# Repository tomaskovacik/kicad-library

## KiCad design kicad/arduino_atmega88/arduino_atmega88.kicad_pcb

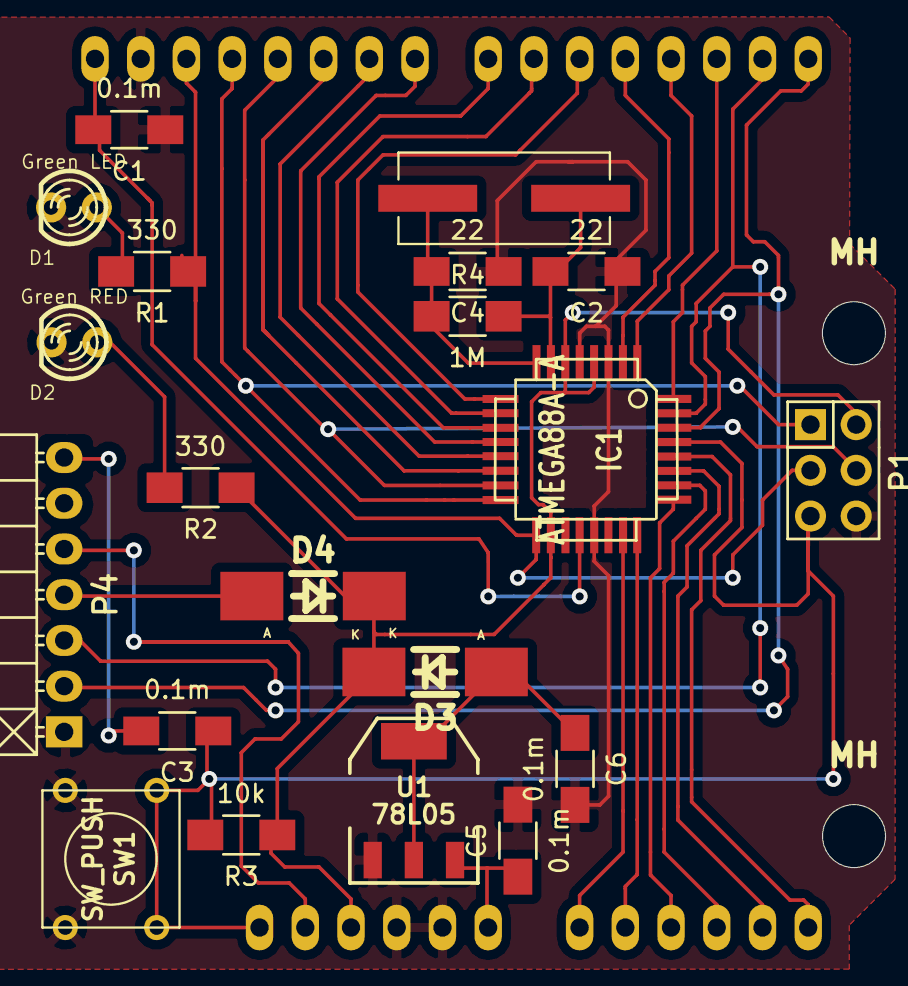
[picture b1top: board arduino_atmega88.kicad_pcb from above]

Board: 2 copper layers, 25 parts (0 on the bottom side), 33 nets.

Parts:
C1, C3, C5, C6: 0.1m; C_1206_HandSoldering
C2, C4: 22; C_1206_HandSoldering
D1: Green LED; LED-3MM
D2: Green RED; LED-3MM
D3, D4: 1N4148; Diode-MELF_Handsoldering
IC1: ATMEGA88A-A; TQFP-32
MH: MountingHole_3-5mm_RevA_Date21Jun2010; MountingHole_3-5mm
MH#2, MH#3, MH#4: MountingHole_3-5mm_RevA_Date21Jun2010; MountingHole_3-5mm
P1: CONN_6; Pin_Header_Straight_2x03
P4: CONN_7; Pin_Header_Angled_1x07
R1, R2: 330; R_1206_HandSoldering
R3: 10k; R_1206_HandSoldering
R4: 1M; R_1206_HandSoldering
SHIELD1: ARDUINO_SHIELD; ARDUINO_SHIELD_2_040pins
SW1: SW_PUSH; SW_PUSH_SMALL
U1: 78L05; SOT-223-REGULATOR
X1: 16MHz; xtal2-11.5mmx4.83mm

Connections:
+3.3V: P4.5, SHIELD1.3V3
+5V: D3.2, D4.2, IC1.4, IC1.6, IC1.18, P1.2, R2.1, R3.1, SHIELD1.5V
/A0: IC1.23, SHIELD1.AD0
/A1: IC1.24, SHIELD1.AD1
/A2: IC1.25, SHIELD1.AD2
/A3: IC1.26, SHIELD1.AD3
/A4: IC1.27, SHIELD1.AD4
/A5: IC1.28, SHIELD1.AD5
/AREF: C1.2, IC1.20, SHIELD1.AREF
/D2: IC1.32, SHIELD1.2
/D3: IC1.1, SHIELD1.3
/D4: IC1.2, SHIELD1.4
/D5: IC1.9, SHIELD1.5
/D6: IC1.10, SHIELD1.6
/D7: IC1.11, SHIELD1.7
/D8: IC1.12, SHIELD1.8
/D9: IC1.13, SHIELD1.9
/D10: IC1.14, SHIELD1.10
/DTR: C3.2, P4.7
/MISO: IC1.16, P1.1, SHIELD1.12
/MOSI: IC1.15, P1.4, SHIELD1.11
/RESET: C3.1, IC1.29, P1.5, R3.2, SHIELD1.RST, SW1.1
/RX: IC1.30, P4.2, SHIELD1.0
/SCK: IC1.17, P1.3, R1.1, SHIELD1.13
/TX: IC1.31, P4.3, SHIELD1.1
/Vin: C5.1, SHIELD1.V_IN, U1.VI
GND: C1.1, C2.1, C4.1, C5.2, C6.2, D1.2, D2.2, IC1.3, IC1.5, IC1.21, P1.6, P4.1, SHIELD1.GND1, SHIELD1.GND2, SHIELD1.GND3, SW1.2, U1.GND
unnamed: C2.2, IC1.7, R4.2, X1.1
unnamed: C4.2, IC1.8, R4.1, X1.2
unnamed: C6.1, D3.1, U1.VO
unnamed: D1.1, R1.2
unnamed: D2.1, R2.2
unnamed: D4.1, P4.4

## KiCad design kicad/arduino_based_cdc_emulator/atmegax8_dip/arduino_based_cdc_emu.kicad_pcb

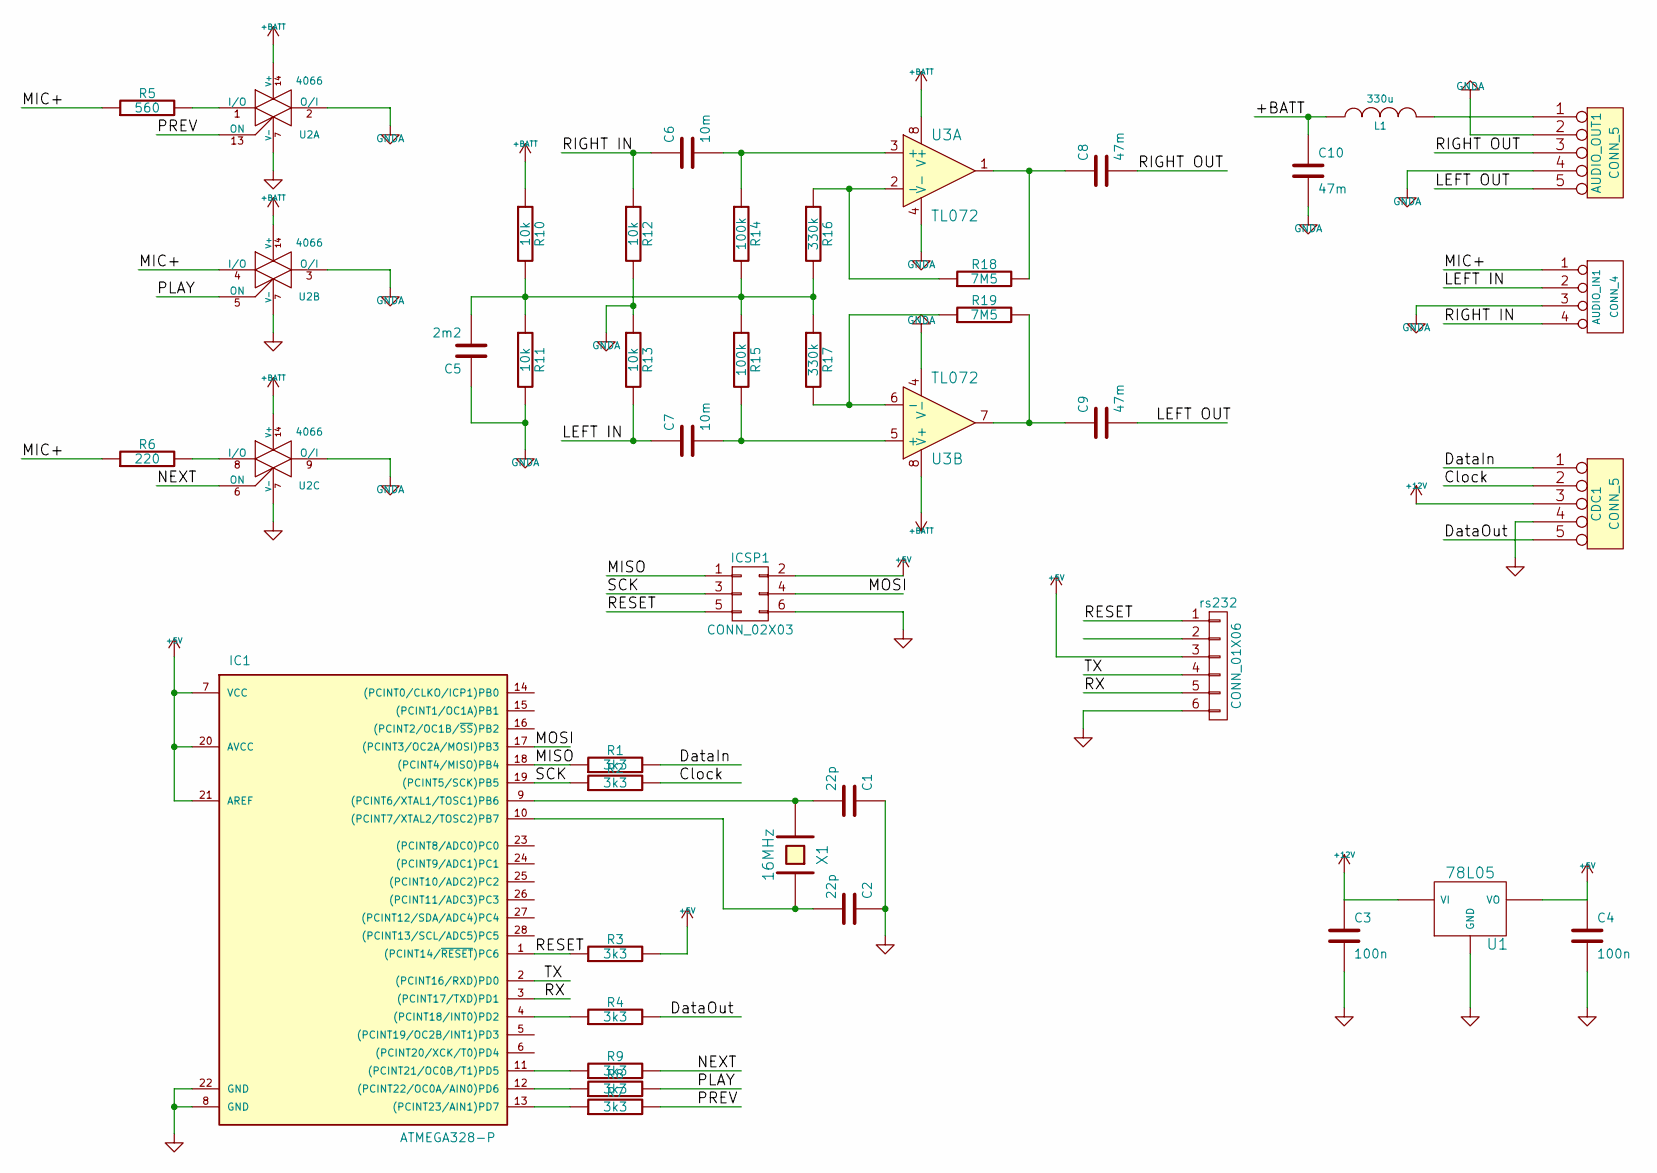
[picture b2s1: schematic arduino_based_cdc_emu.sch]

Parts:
AUDIO_IN1: CONN_4; Pin_Header_Straight_1x04
AUDIO_OUT1: CONN_5; Pin_Header_Straight_1x05
C1, C2: 22p; C1
C3, C4: 100n; C1
C5: 2m2; C1V5
C6, C7: 10m; C1V8
C8, C9, C10: 47m; C2V8
CDC1: CONN_5; Pin_Header_Straight_1x05
IC1: ATMEGA328-P; DIP-28__300
ICSP1: CONN_02X03; Pin_Header_Straight_2x03
L1: 330u; R3-5
R1, R2, R3, R4, R7, R8, R9: 3k3; R3
R5: 560; R3
R6: 220; R3
R10, R11, R12: 10k; R3
R13: 10k; Resistor_Vertical_RM5mm
R14, R15: 100k; R3
R16, R17: 330k; R3
R18, R19: 7M5; R3
U1: 78L05; TO92-STABIL
U2: 4066; DIP-14__300
U3: TL072; DIP-8__300
X1: 16MHz; HC-49V
rs232: CONN_01X06; Pin_Header_Straight_1x06

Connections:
+5V: C4.1, IC1.7 (VCC), IC1.20 (AVCC), IC1.21 (AREF), ICSP1.2, R3.2, U1.VO, rs232.3
+12V: C3.1, CDC1.3, U1.VI
+BATT: C10.1, L1.1, R10.1, U2.14 (V+), U3.8 (V+)
/Clock: CDC1.2, R2.2
/DataIn: CDC1.1, R1.2
/DataOut: CDC1.5, R4.2
/LEFT IN: AUDIO_IN1.2, C7.1, R13.2
/LEFT OUT: AUDIO_OUT1.5, C9.2
/MIC+: AUDIO_IN1.1, R5.1, R6.1, U2.4 (I/O)
/MISO: IC1.18 ((PCINT4/MISO)PB4), ICSP1.1, R1.1
/MOSI: IC1.17 ((PCINT3/OC2A/MOSI)PB3), ICSP1.4
/NEXT: R9.2, U2.6 (ON)
/PLAY: R8.2, U2.5 (ON)
/PREV: R7.2, U2.13 (ON)
/RESET: IC1.1 ((PCINT14/~RESET~)PC6), ICSP1.5, R3.1, rs232.1
/RIGHT IN: AUDIO_IN1.4, C6.1, R12.1
/RIGHT OUT: AUDIO_OUT1.3, C8.2
/RX: IC1.3 ((PCINT17/TXD)PD1), rs232.5
/SCK: IC1.19 ((PCINT5/SCK)PB5), ICSP1.3, R2.1
/TX: IC1.2 ((PCINT16/RXD)PD0), rs232.4
GND: C1.1, C2.1, C3.2, C4.2, CDC1.4, IC1.8 (GND), IC1.22 (GND), ICSP1.6, U1.GND, U2.7 (V-), rs232.6
GNDA: AUDIO_IN1.3, AUDIO_OUT1.2, AUDIO_OUT1.4, C5.1, C10.2, R11.2, R12.2, R13.1, U2.2 (O/I), U2.3 (O/I), U2.9 (O/I), U3.4 (V-)
unnamed: AUDIO_OUT1.1, L1.2
unnamed: C1.2, IC1.9 ((PCINT6/XTAL1/TOSC1)PB6), X1.2
unnamed: C2.2, IC1.10 ((PCINT7/XTAL2/TOSC2)PB7), X1.1
unnamed: C5.2, R10.2, R11.1, R14.2, R15.1, R16.2, R17.1
unnamed: C6.2, R14.1, U3.3 (+)
unnamed: C7.2, R15.2, U3.5 (+)
unnamed: C8.1, R18.2, U3.1
unnamed: C9.1, R19.2, U3.7
unnamed: IC1.4 ((PCINT18/INT0)PD2), R4.1
unnamed: IC1.11 ((PCINT21/OC0B/T1)PD5), R9.1
unnamed: IC1.12 ((PCINT22/OC0A/AIN0)PD6), R8.1
unnamed: IC1.13 ((PCINT23/AIN1)PD7), R7.1
unnamed: R5.2, U2.1 (I/O)
unnamed: R6.2, U2.8 (I/O)
unnamed: R16.1, R18.1, U3.2 (-)
unnamed: R17.2, R19.1, U3.6 (-)

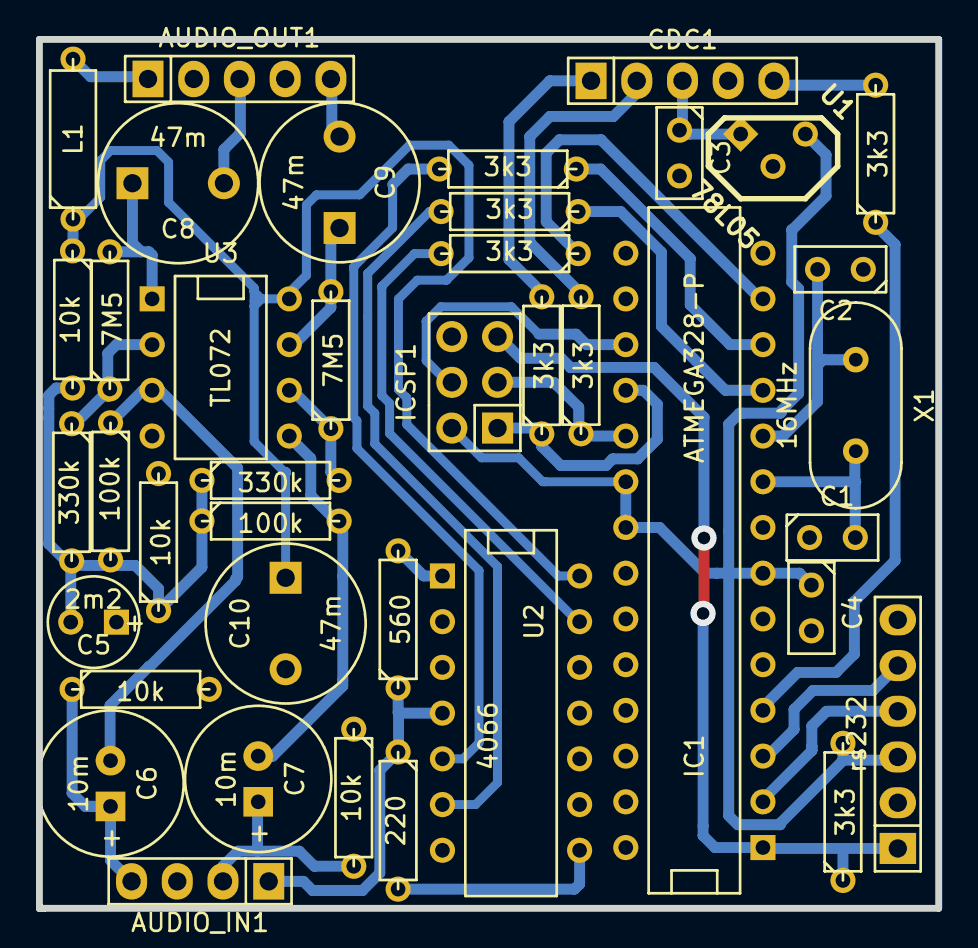
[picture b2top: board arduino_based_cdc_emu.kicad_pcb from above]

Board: 2 copper layers, 50.0 x 48.3 mm, 40 parts (0 on the bottom side), 38 nets.

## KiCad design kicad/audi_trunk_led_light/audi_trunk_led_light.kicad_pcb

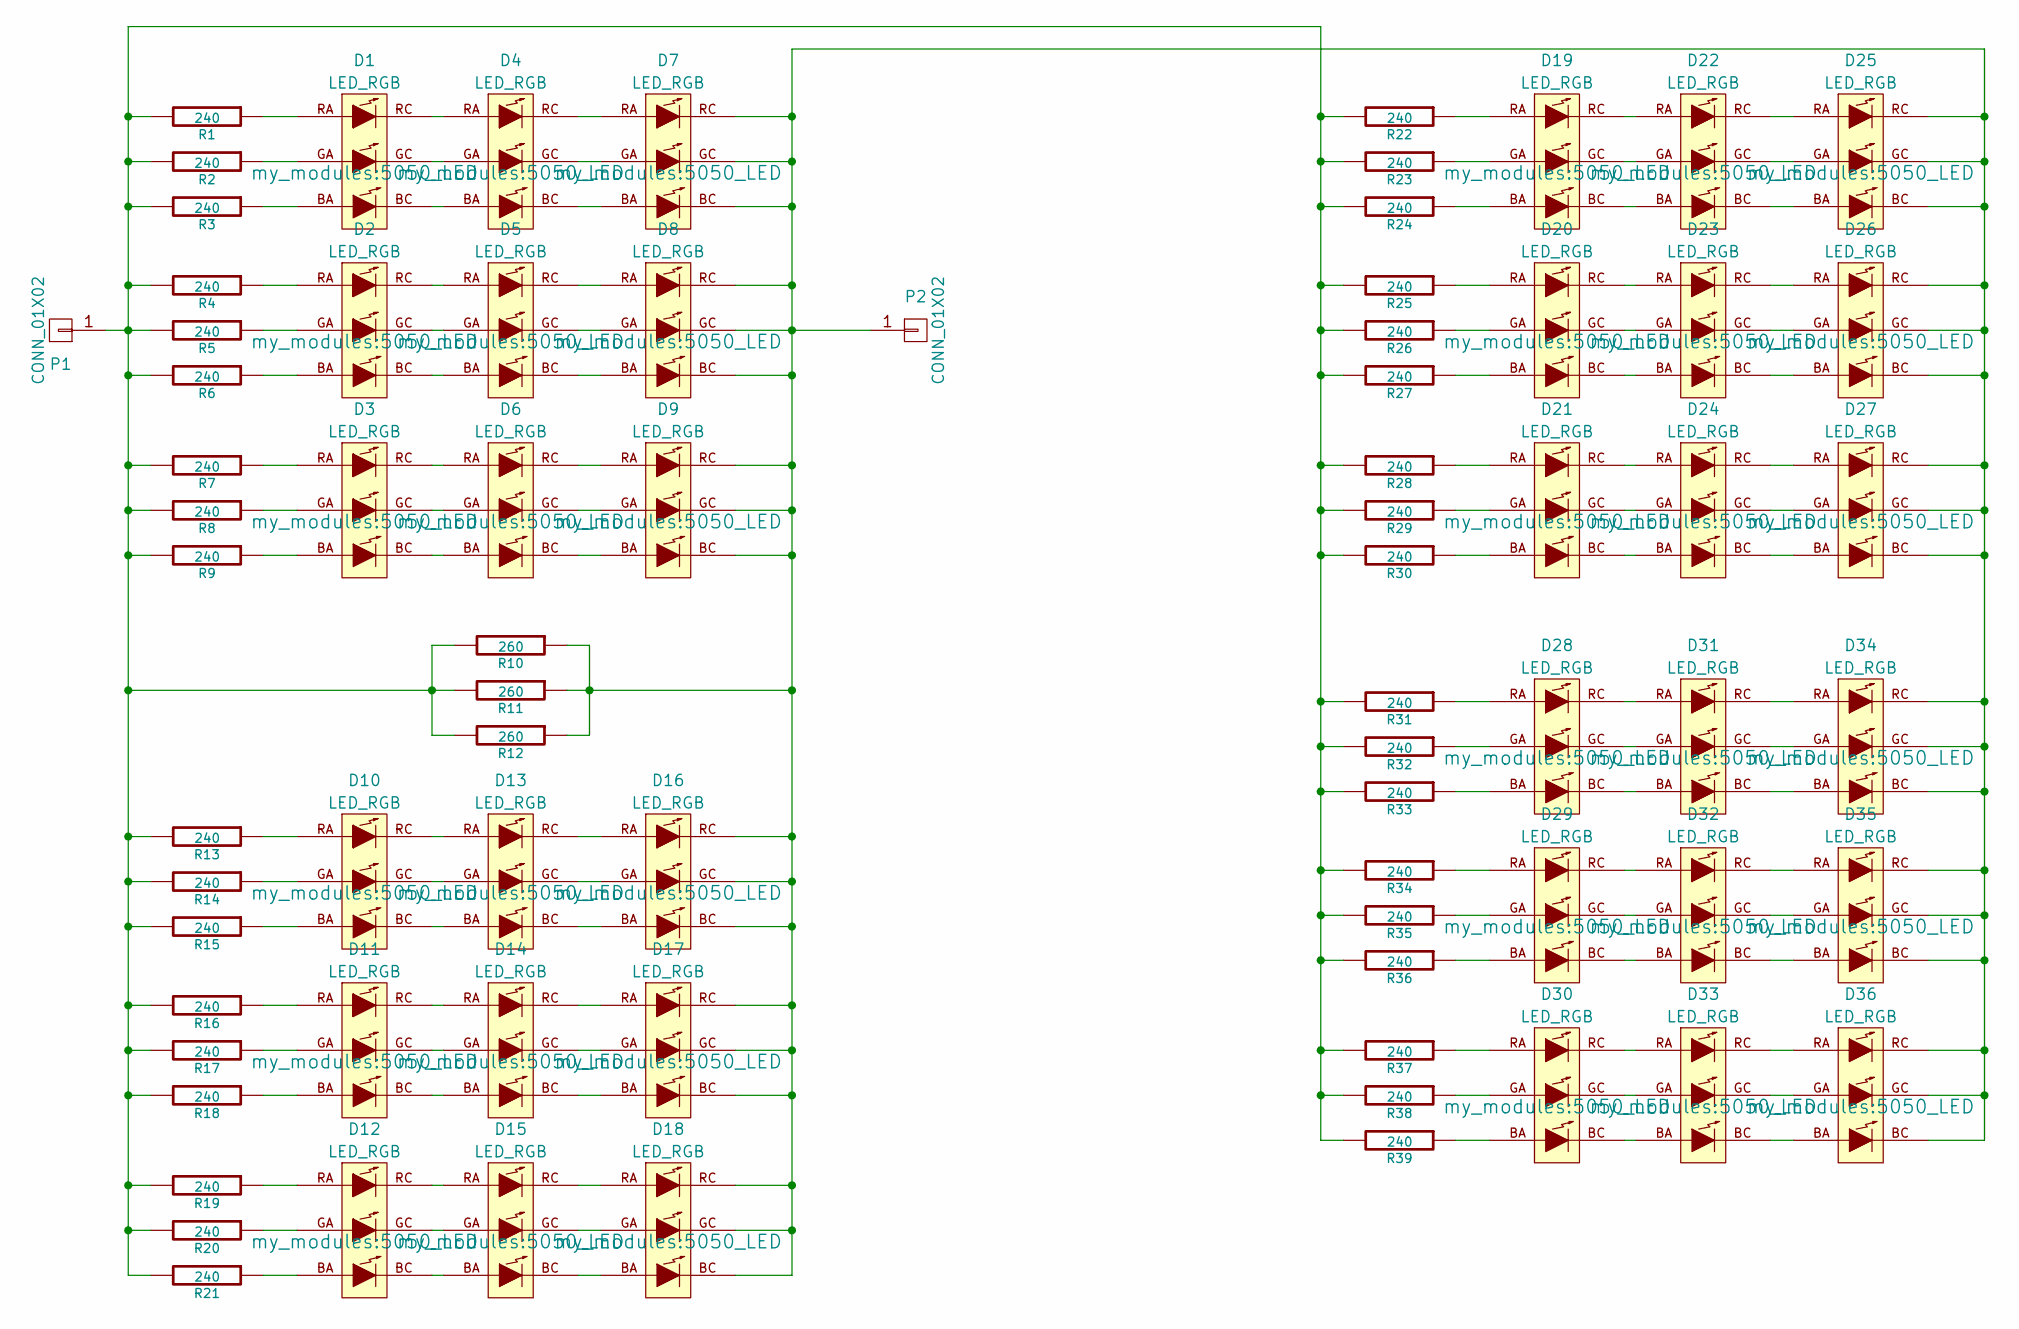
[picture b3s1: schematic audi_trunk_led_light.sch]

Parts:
D1, D2, D3, D4, D5, D6, D7, D8, D9, D10, D11, D12, D13, D14, D15, D16, D17, D18, D19, D20, D21, D22, D23, D24, D25, D26, D27, D28, D29, D30, D31, D32, D33, D34, D35, D36: LED_RGB; 5050_LED
P1, P2: CONN_01X02
R1, R2, R3, R4, R5, R6, R7, R8, R9, R13, R14, R15, R16, R17, R18, R19, R20, R21, R22, R23, R24, R25, R26, R27, R28, R29, R30, R31, R32, R33, R34, R35, R36, R37, R38, R39: 240
R10, R11, R12: 260

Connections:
unnamed: D1.BA (BLUE_ANODE), R3.1
unnamed: D1.BC (BLUE_CATHODE), D4.BA (BLUE_ANODE)
unnamed: D1.GA (GREEN_ANODE), R2.1
unnamed: D1.GC (GREEN_CATHODE), D4.GA (GREEN_ANODE)
unnamed: D1.RA (RED_ANODE), R1.1
unnamed: D1.RC (RED_CATHODE), D4.RA (RED_ANODE)
unnamed: D2.BA (BLUE_ANODE), R6.1
unnamed: D2.BC (BLUE_CATHODE), D5.BA (BLUE_ANODE)
unnamed: D2.GA (GREEN_ANODE), R5.1
unnamed: D2.GC (GREEN_CATHODE), D5.GA (GREEN_ANODE)
unnamed: D2.RA (RED_ANODE), R4.1
unnamed: D2.RC (RED_CATHODE), D5.RA (RED_ANODE)
unnamed: D3.BA (BLUE_ANODE), R9.1
unnamed: D3.BC (BLUE_CATHODE), D6.BA (BLUE_ANODE)
unnamed: D3.GA (GREEN_ANODE), R8.1
unnamed: D3.GC (GREEN_CATHODE), D6.GA (GREEN_ANODE)
unnamed: D3.RA (RED_ANODE), R7.1
unnamed: D3.RC (RED_CATHODE), D6.RA (RED_ANODE)
unnamed: D4.BC (BLUE_CATHODE), D7.BA (BLUE_ANODE)
unnamed: D4.GC (GREEN_CATHODE), D7.GA (GREEN_ANODE)
unnamed: D4.RC (RED_CATHODE), D7.RA (RED_ANODE)
unnamed: D5.BC (BLUE_CATHODE), D8.BA (BLUE_ANODE)
unnamed: D5.GC (GREEN_CATHODE), D8.GA (GREEN_ANODE)
unnamed: D5.RC (RED_CATHODE), D8.RA (RED_ANODE)
unnamed: D6.BC (BLUE_CATHODE), D9.BA (BLUE_ANODE)
unnamed: D6.GC (GREEN_CATHODE), D9.GA (GREEN_ANODE)
unnamed: D6.RC (RED_CATHODE), D9.RA (RED_ANODE)
unnamed: D10.BA (BLUE_ANODE), R15.1
unnamed: D10.BC (BLUE_CATHODE), D13.BA (BLUE_ANODE)
unnamed: D10.GA (GREEN_ANODE), R14.1
unnamed: D10.GC (GREEN_CATHODE), D13.GA (GREEN_ANODE)
unnamed: D10.RA (RED_ANODE), R13.1
unnamed: D10.RC (RED_CATHODE), D13.RA (RED_ANODE)
unnamed: D11.BA (BLUE_ANODE), R18.1
unnamed: D11.BC (BLUE_CATHODE), D14.BA (BLUE_ANODE)
unnamed: D11.GA (GREEN_ANODE), R17.1
unnamed: D11.GC (GREEN_CATHODE), D14.GA (GREEN_ANODE)
unnamed: D11.RA (RED_ANODE), R16.1
unnamed: D11.RC (RED_CATHODE), D14.RA (RED_ANODE)
unnamed: D12.BA (BLUE_ANODE), R21.1
unnamed: D12.BC (BLUE_CATHODE), D15.BA (BLUE_ANODE)
unnamed: D12.GA (GREEN_ANODE), R20.1
unnamed: D12.GC (GREEN_CATHODE), D15.GA (GREEN_ANODE)
unnamed: D12.RA (RED_ANODE), R19.1
unnamed: D12.RC (RED_CATHODE), D15.RA (RED_ANODE)
unnamed: D13.BC (BLUE_CATHODE), D16.BA (BLUE_ANODE)
unnamed: D13.GC (GREEN_CATHODE), D16.GA (GREEN_ANODE)
unnamed: D13.RC (RED_CATHODE), D16.RA (RED_ANODE)
unnamed: D14.BC (BLUE_CATHODE), D17.BA (BLUE_ANODE)
unnamed: D14.GC (GREEN_CATHODE), D17.GA (GREEN_ANODE)
unnamed: D14.RC (RED_CATHODE), D17.RA (RED_ANODE)
unnamed: D15.BC (BLUE_CATHODE), D18.BA (BLUE_ANODE)
unnamed: D15.GC (GREEN_CATHODE), D18.GA (GREEN_ANODE)
unnamed: D15.RC (RED_CATHODE), D18.RA (RED_ANODE)
unnamed: D7.BC (BLUE_CATHODE), D7.GC (GREEN_CATHODE), D7.RC (RED_CATHODE), D8.BC (BLUE_CATHODE), D8.GC (GREEN_CATHODE), D8.RC (RED_CATHODE), D9.BC (BLUE_CATHODE), D9.GC (GREEN_CATHODE), D9.RC (RED_CATHODE), D16.BC (BLUE_CATHODE), D16.GC (GREEN_CATHODE), D16.RC (RED_CATHODE), D17.BC (BLUE_CATHODE), D17.GC (GREEN_CATHODE), D17.RC (RED_CATHODE), D18.BC (BLUE_CATHODE), D18.GC (GREEN_CATHODE), D18.RC (RED_CATHODE), D25.BC (BLUE_CATHODE), D25.GC (GREEN_CATHODE), D25.RC (RED_CATHODE), D26.BC (BLUE_CATHODE), D26.GC (GREEN_CATHODE), D26.RC (RED_CATHODE), D27.BC (BLUE_CATHODE), D27.GC (GREEN_CATHODE), D27.RC (RED_CATHODE), D34.BC (BLUE_CATHODE), D34.GC (GREEN_CATHODE), D34.RC (RED_CATHODE), D35.BC (BLUE_CATHODE), D35.GC (GREEN_CATHODE), D35.RC (RED_CATHODE), D36.BC (BLUE_CATHODE), D36.GC (GREEN_CATHODE), D36.RC (RED_CATHODE), P2.1, R10.1, R11.1, R12.1
unnamed: D19.BA (BLUE_ANODE), R24.1
unnamed: D19.BC (BLUE_CATHODE), D22.BA (BLUE_ANODE)
unnamed: D19.GA (GREEN_ANODE), R23.1
unnamed: D19.GC (GREEN_CATHODE), D22.GA (GREEN_ANODE)
unnamed: D19.RA (RED_ANODE), R22.1
unnamed: D19.RC (RED_CATHODE), D22.RA (RED_ANODE)
unnamed: D20.BA (BLUE_ANODE), R27.1
unnamed: D20.BC (BLUE_CATHODE), D23.BA (BLUE_ANODE)
unnamed: D20.GA (GREEN_ANODE), R26.1
unnamed: D20.GC (GREEN_CATHODE), D23.GA (GREEN_ANODE)
unnamed: D20.RA (RED_ANODE), R25.1
unnamed: D20.RC (RED_CATHODE), D23.RA (RED_ANODE)
unnamed: D21.BA (BLUE_ANODE), R30.1
unnamed: D21.BC (BLUE_CATHODE), D24.BA (BLUE_ANODE)
unnamed: D21.GA (GREEN_ANODE), R29.1
unnamed: D21.GC (GREEN_CATHODE), D24.GA (GREEN_ANODE)
unnamed: D21.RA (RED_ANODE), R28.1
unnamed: D21.RC (RED_CATHODE), D24.RA (RED_ANODE)
unnamed: D22.BC (BLUE_CATHODE), D25.BA (BLUE_ANODE)
unnamed: D22.GC (GREEN_CATHODE), D25.GA (GREEN_ANODE)
unnamed: D22.RC (RED_CATHODE), D25.RA (RED_ANODE)
unnamed: D23.BC (BLUE_CATHODE), D26.BA (BLUE_ANODE)
unnamed: D23.GC (GREEN_CATHODE), D26.GA (GREEN_ANODE)
unnamed: D23.RC (RED_CATHODE), D26.RA (RED_ANODE)
unnamed: D24.BC (BLUE_CATHODE), D27.BA (BLUE_ANODE)
unnamed: D24.GC (GREEN_CATHODE), D27.GA (GREEN_ANODE)
unnamed: D24.RC (RED_CATHODE), D27.RA (RED_ANODE)
unnamed: D28.BA (BLUE_ANODE), R33.1
unnamed: D28.BC (BLUE_CATHODE), D31.BA (BLUE_ANODE)
unnamed: D28.GA (GREEN_ANODE), R32.1
unnamed: D28.GC (GREEN_CATHODE), D31.GA (GREEN_ANODE)
unnamed: D28.RA (RED_ANODE), R31.1
unnamed: D28.RC (RED_CATHODE), D31.RA (RED_ANODE)
unnamed: D29.BA (BLUE_ANODE), R36.1
unnamed: D29.BC (BLUE_CATHODE), D32.BA (BLUE_ANODE)
unnamed: D29.GA (GREEN_ANODE), R35.1
unnamed: D29.GC (GREEN_CATHODE), D32.GA (GREEN_ANODE)
unnamed: D29.RA (RED_ANODE), R34.1
unnamed: D29.RC (RED_CATHODE), D32.RA (RED_ANODE)
unnamed: D30.BA (BLUE_ANODE), R39.1
unnamed: D30.BC (BLUE_CATHODE), D33.BA (BLUE_ANODE)
unnamed: D30.GA (GREEN_ANODE), R38.1
unnamed: D30.GC (GREEN_CATHODE), D33.GA (GREEN_ANODE)
unnamed: D30.RA (RED_ANODE), R37.1
unnamed: D30.RC (RED_CATHODE), D33.RA (RED_ANODE)
unnamed: D31.BC (BLUE_CATHODE), D34.BA (BLUE_ANODE)
unnamed: D31.GC (GREEN_CATHODE), D34.GA (GREEN_ANODE)
unnamed: D31.RC (RED_CATHODE), D34.RA (RED_ANODE)
unnamed: D32.BC (BLUE_CATHODE), D35.BA (BLUE_ANODE)
unnamed: D32.GC (GREEN_CATHODE), D35.GA (GREEN_ANODE)
unnamed: D32.RC (RED_CATHODE), D35.RA (RED_ANODE)
unnamed: D33.BC (BLUE_CATHODE), D36.BA (BLUE_ANODE)
unnamed: D33.GC (GREEN_CATHODE), D36.GA (GREEN_ANODE)
unnamed: D33.RC (RED_CATHODE), D36.RA (RED_ANODE)
unnamed: P1.1, R1.2, R2.2, R3.2, R4.2, R5.2, R6.2, R7.2, R8.2, R9.2, R10.2, R11.2, R12.2, R13.2, R14.2, R15.2, R16.2, R17.2, R18.2, R19.2, R20.2, R21.2, R22.2, R23.2, R24.2, R25.2, R26.2, R27.2, R28.2, R29.2, R30.2, R31.2, R32.2, R33.2, R34.2, R35.2, R36.2, R37.2, R38.2, R39.2

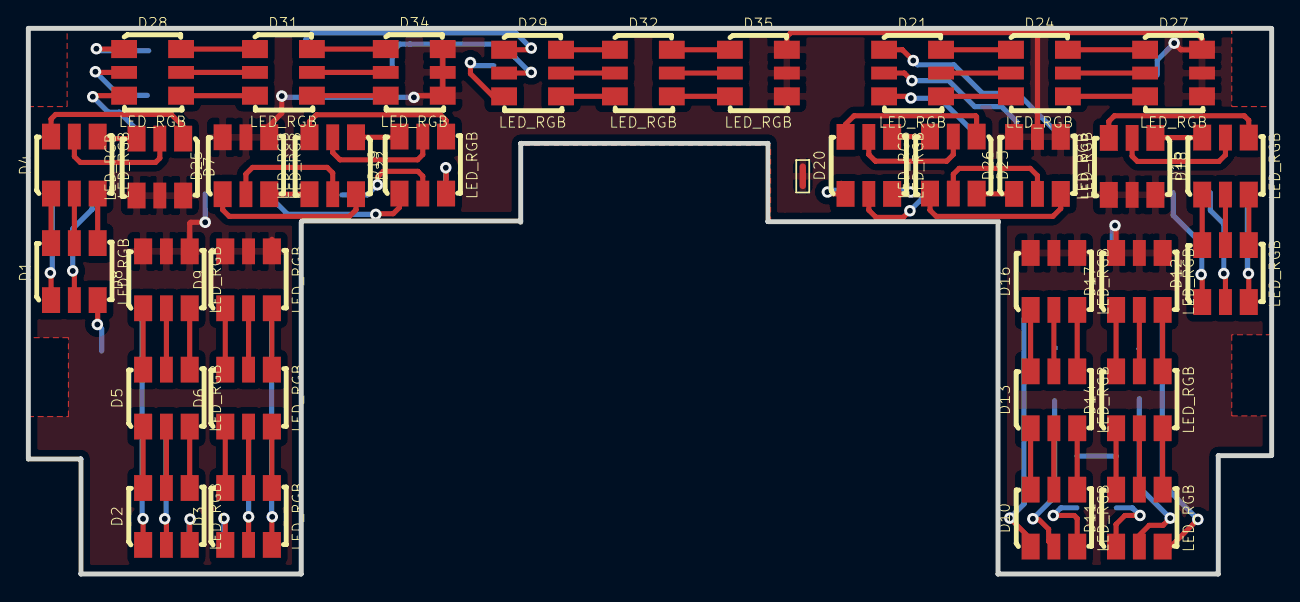
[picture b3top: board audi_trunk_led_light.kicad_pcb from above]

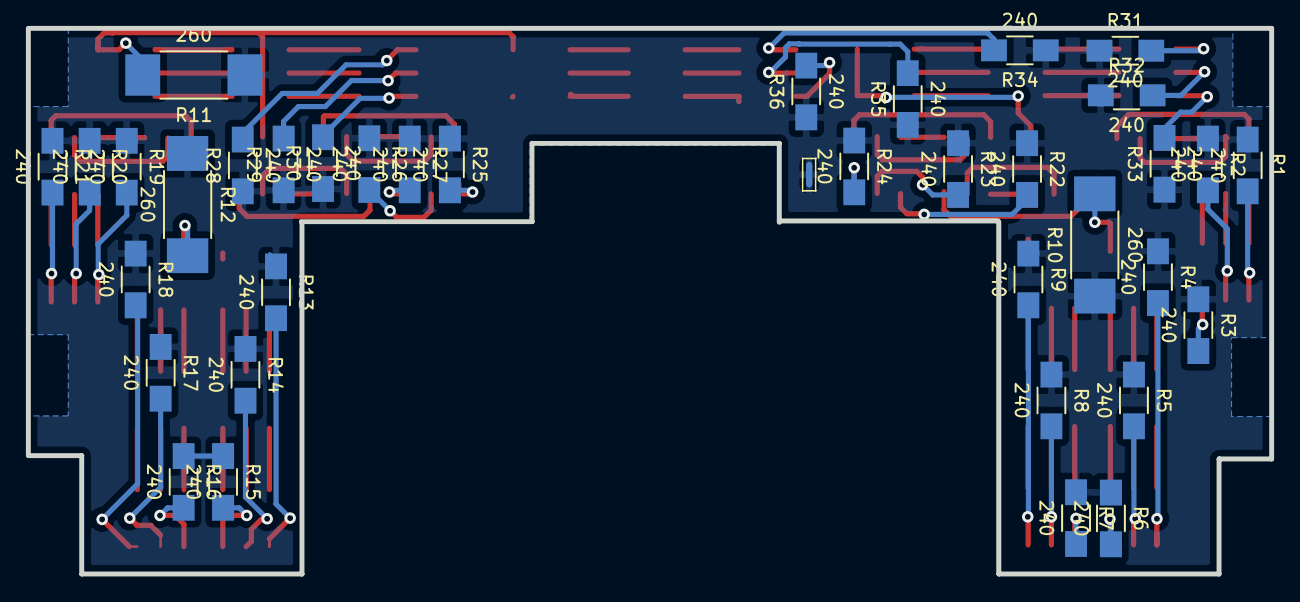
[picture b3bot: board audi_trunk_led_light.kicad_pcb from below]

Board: 2 copper layers, 96.1 x 42.2 mm, 71 parts (37 on the bottom side), 101 nets.

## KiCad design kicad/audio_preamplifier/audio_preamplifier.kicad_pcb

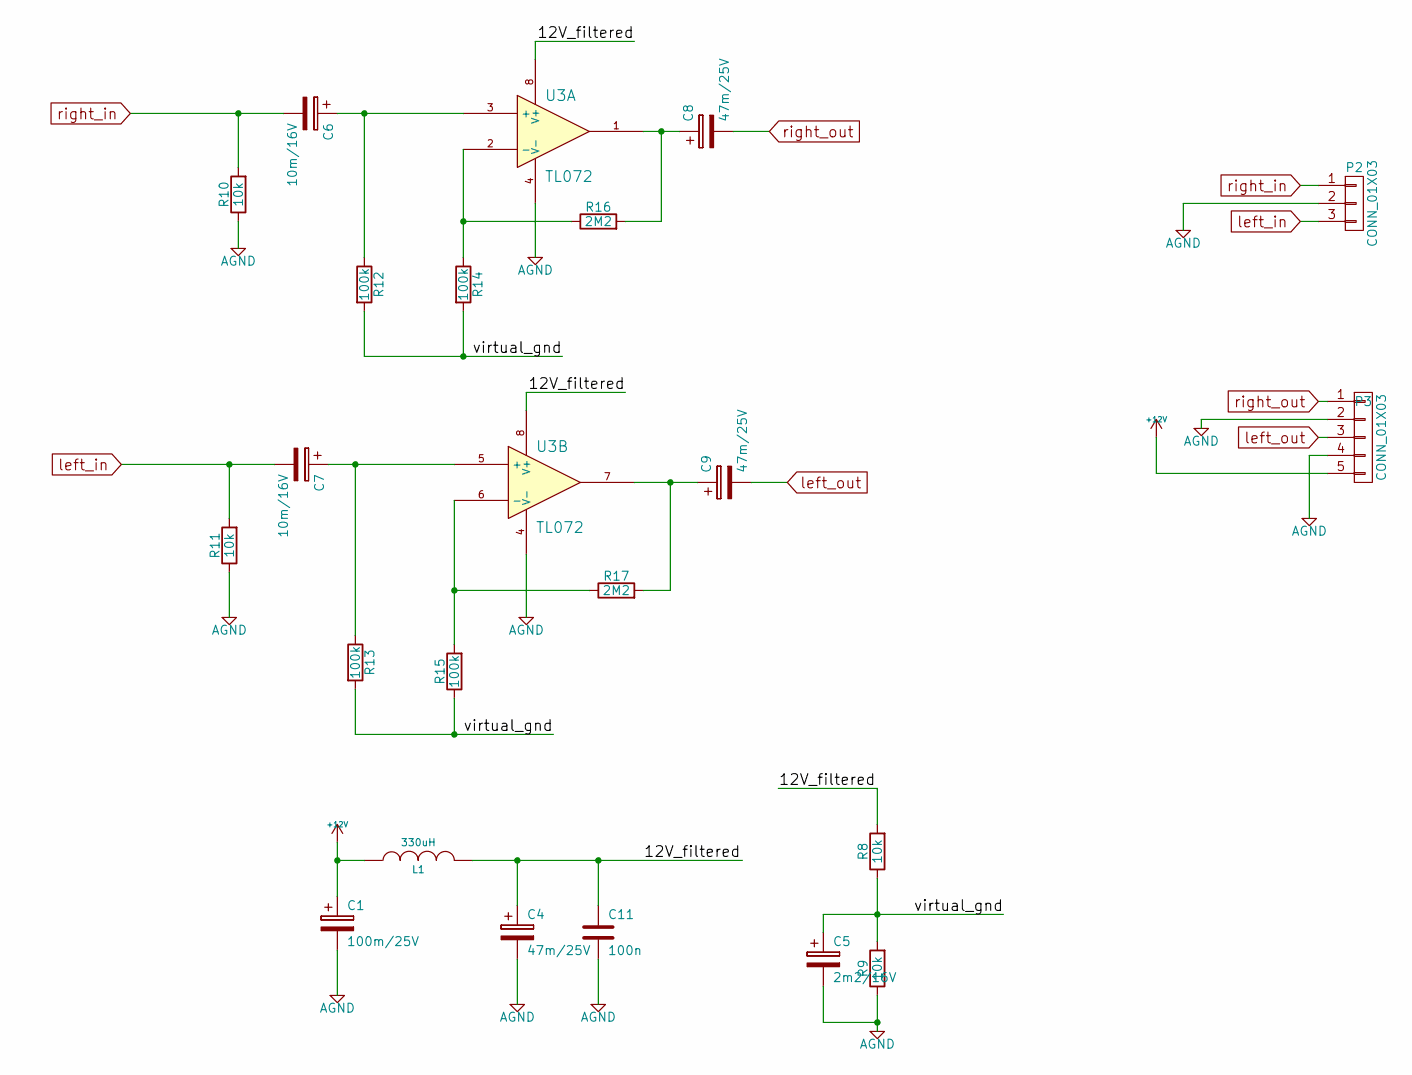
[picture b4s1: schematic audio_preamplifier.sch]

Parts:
C1: 100m/25V; c_elec_6.3x7.7
C4: 47m/25V; TantalC_SizeD_EIA-7343_HandSoldering
C5: 2m2/16V; TantalC_SizeA_EIA-3216_HandSoldering
C6, C7: 10m/16V; c_elec_5x5.8
C8, C9: 47m/25V; c_elec_5x5.8
C11: 100n; C_1206_HandSoldering
L1: 330uH
P2: CONN_01X03; Pin_Header_Straight_1x03
P3: CONN_01X03; Pin_Header_Straight_1x05
R8, R9, R10, R11: 10k; R_1206_HandSoldering
R12, R13, R14, R15: 100k; R_1206_HandSoldering
R16, R17: 2M2; R_1206_HandSoldering
U3: TL072

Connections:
+12V: C1.1, L1.1, P3.5
/12V_filtered: C4.1, C11.1, L1.2, R8.2, U3.8 (V+)
/virtual_gnd: C5.1, R8.1, R9.2, R12.2, R13.2, R14.2, R15.1
AGND: C1.2, C4.2, C5.2, C11.2, P2.2, P3.2, P3.4, R9.1, R10.1, R11.1, U3.4 (V-)
unnamed: C6.1, R12.1, U3.3 (+)
unnamed: C7.1, R13.1, U3.5 (+)
unnamed: C8.1, R16.2, U3.1
unnamed: C9.1, R17.2, U3.7
unnamed: R14.1, R16.1, U3.2 (-)
unnamed: R15.2, R17.1, U3.6 (-)
left_in: C7.2, P2.3, R11.2
left_out: C9.2, P3.3
right_in: C6.2, P2.1, R10.2
right_out: C8.2, P3.1

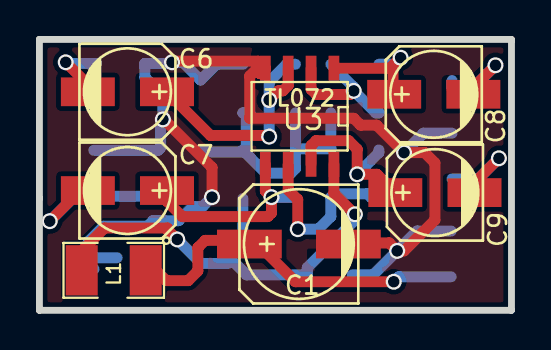
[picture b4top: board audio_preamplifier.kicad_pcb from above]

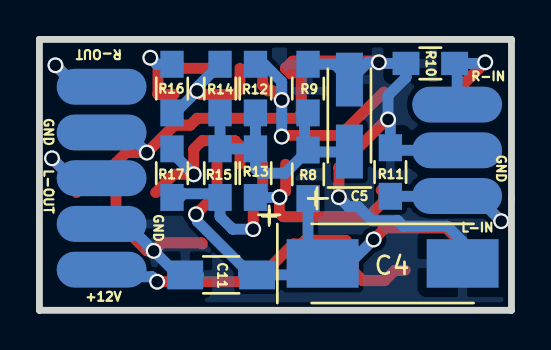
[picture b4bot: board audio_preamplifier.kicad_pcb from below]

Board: 2 copper layers, 26.2 x 15.0 mm, 22 parts (13 on the bottom side), 14 nets.

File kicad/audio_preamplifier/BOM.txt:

R8,R9,
R10,R11     10k smd 0805
R12,R13,
R14,R15     100k smd 0805
R16,R17     2M2 smd 0805

C1              100m/25V 6.3x7.7mm smd elec.
C4              47m/25V sizeD smd tantal
C5              2m2/16V
C6,C7         10m/16V 5x5.8mm  smd elec.
C8,C9         47m/25V 5x5.8mm  smd elec.
C11             100n/50V 0805

L1                330uH smd 1210

U3               TL072/NE5532/equiv. smd SO8

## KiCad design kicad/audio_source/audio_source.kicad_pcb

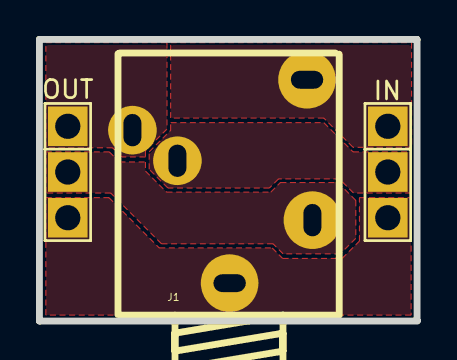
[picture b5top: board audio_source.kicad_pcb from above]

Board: 2 copper layers, 21.0 x 15.6 mm, 3 parts (0 on the bottom side), 5 nets.

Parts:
J1: SCJ368R1NUS0B00G; SCJ-0354-5PU
P1: IN; Pin_Header_Straight_1x03
P2: OUT; Pin_Header_Straight_1x03

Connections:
AGND: J1.1, P1.3, P2.3
CD_left_in: J1.4, P1.1
CD_right_in: J1.3, P1.2
RADIO_left_out: J1.5, P2.2
RADIO_right_out: J1.2, P2.1

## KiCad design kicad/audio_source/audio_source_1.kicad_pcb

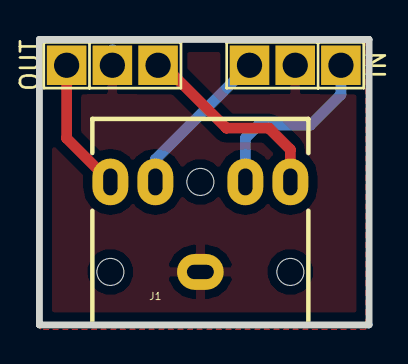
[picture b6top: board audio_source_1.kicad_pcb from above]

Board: 2 copper layers, 18.3 x 15.9 mm, 3 parts (0 on the bottom side), 5 nets.

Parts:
J1: SCJ368R1NUS0B00G; 3.5mm_stereo_jack_PJ306M_no_screw_terminal
P1: IN; Pin_Header_Straight_1x03
P2: OUT; Pin_Header_Straight_1x03

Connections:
AGND: J1.1, P1.2, P2.2
CD_left_in: J1.4, P1.1
CD_right_in: J1.3, P1.3
RADIO_left_out: J1.5, P2.3
RADIO_right_out: J1.2, P2.1
